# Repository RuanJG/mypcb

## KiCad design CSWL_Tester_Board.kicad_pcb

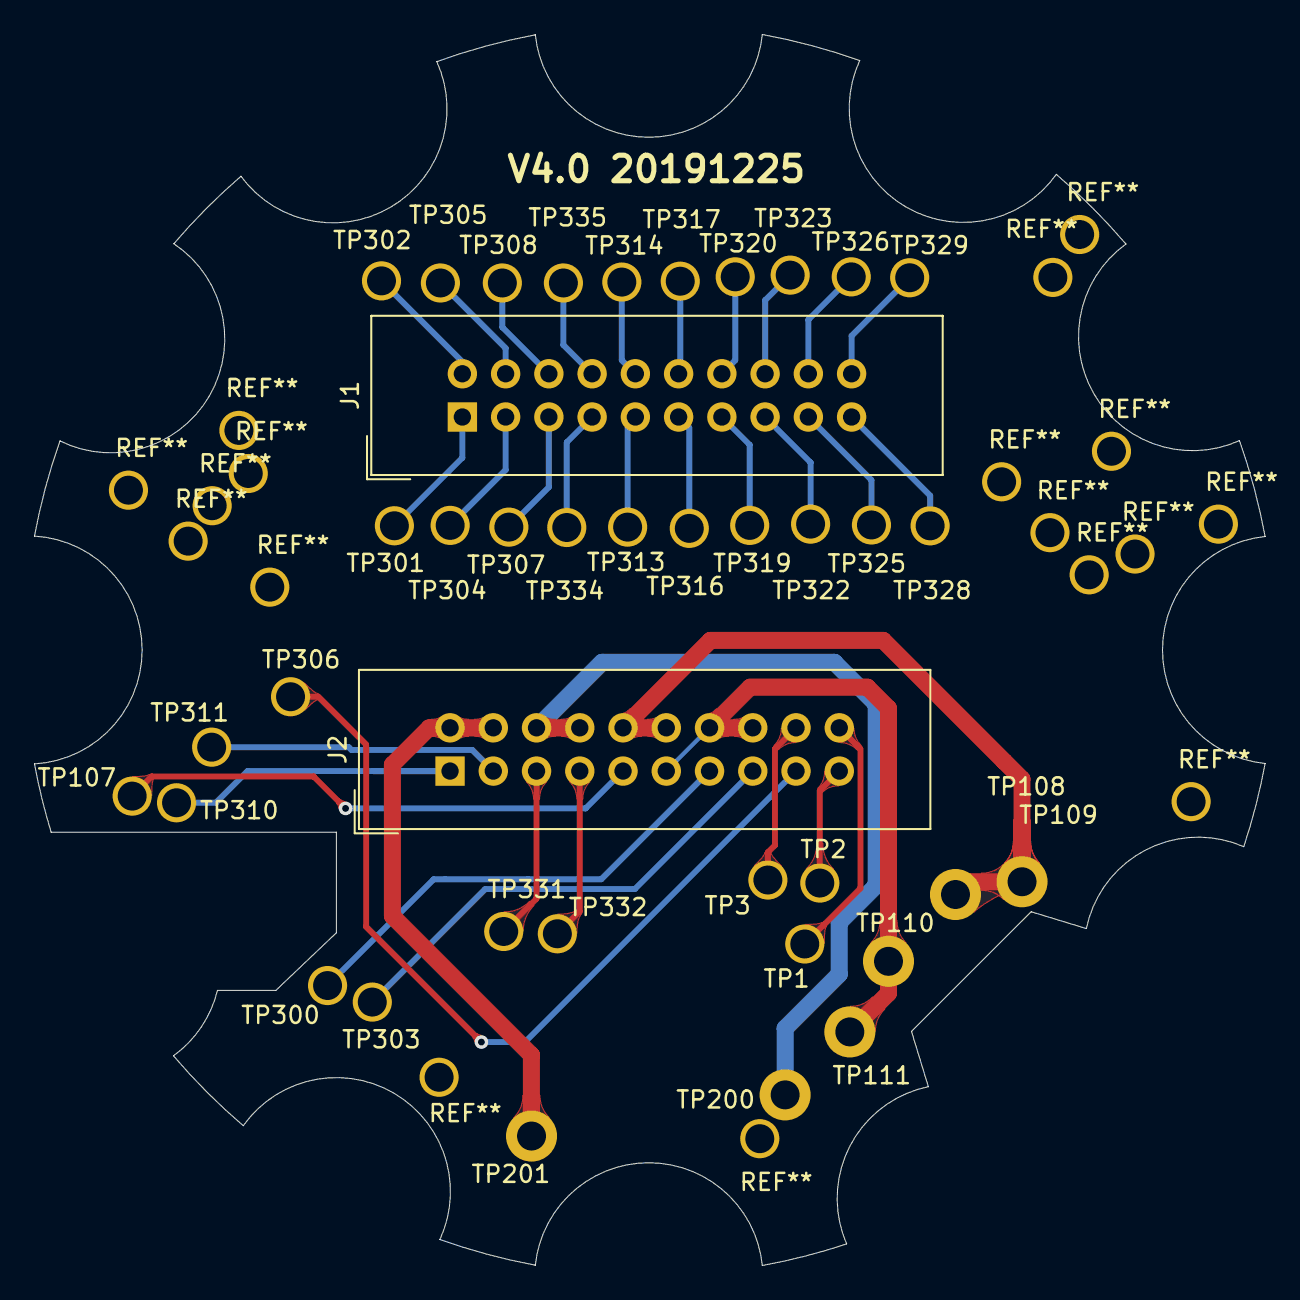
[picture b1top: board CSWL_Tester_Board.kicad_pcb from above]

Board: 2 copper layers, 72.3 x 72.3 mm, 39 parts (0 on the bottom side), 35 nets.

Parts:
J1, J2: Conn_02x10_Odd_Even; IDC-Header_2x10_P2.54mm_Vertical
TP1, TP2, TP3, TP107, TP300, TP301, TP302, TP303, TP304, TP305, TP306, TP307, TP308, TP310, TP311, TP313, TP314, TP316, TP317, TP319, TP320, TP322, TP323, TP325, TP326, TP328, TP329, TP331, TP332, TP334, TP335: TP; PinCard_Hole_D2.3mm_1.3dill
TP108: TP108; PinCard_Hole_D2.3mm_1.3dill
TP109: TP109; PinCard_Hole_D2.3mm_1.3dill
TP110: TP110; PinCard_Hole_D2.3mm_1.3dill
TP111: TP111; PinCard_Hole_D2.3mm_1.3dill
TP200: TP200; PinCard_Hole_D2.3mm_1.3dill
TP201: TP201; PinCard_Hole_D2.3mm_1.3dill

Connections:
/AS4_Y: J2.19, TP1.1
/AS4_Z: J2.20, TP2.1
/CSWL_IN+: J2.10, J2.12, TP108.1, TP109.1
/CSWL_IN-: J2.11, J2.14, J2.16, TP110.1, TP111.1
/CSWL_VDD+: J2.9, TP107.1
/CSWL_Vout+: J2.6, J2.8, TP200.1
/CSWL_Vout-: J2.2, J2.4, TP201.1
/LED1+: J1.1, TP301.1
/LED1-: J1.2, TP302.1
/LED2+: J1.3, TP304.1
/LED2-: J1.4, TP305.1
/LED3+: J1.5, TP307.1
/LED3-: J1.6, TP308.1
/LED4+: J2.1, TP310.1
/LED4-: J2.3, TP311.1
/LED5+: J1.9, TP313.1
/LED5-: J1.10, TP314.1
/LED6+: J1.11, TP316.1
/LED6-: J1.12, TP317.1
/LED7+: J1.13, TP319.1
/LED7-: J1.14, TP320.1
/LED8+: J1.15, TP322.1
/LED8-: J1.16, TP323.1
/LED9+: J1.17, TP325.1
/LED9-: J1.18, TP326.1
/LED10+: J1.19, TP328.1
/LED10-: J1.20, TP329.1
/LED11+: J2.5, TP331.1
/LED11-: J2.7, TP332.1
/LED12+: J1.7, TP334.1
/LED12-: J1.8, TP335.1
/TP300: J2.13, TP300.1
/TP303: J2.15, TP303.1
/TP306: J2.17, TP306.1
/TPXXX: J2.18, TP3.1

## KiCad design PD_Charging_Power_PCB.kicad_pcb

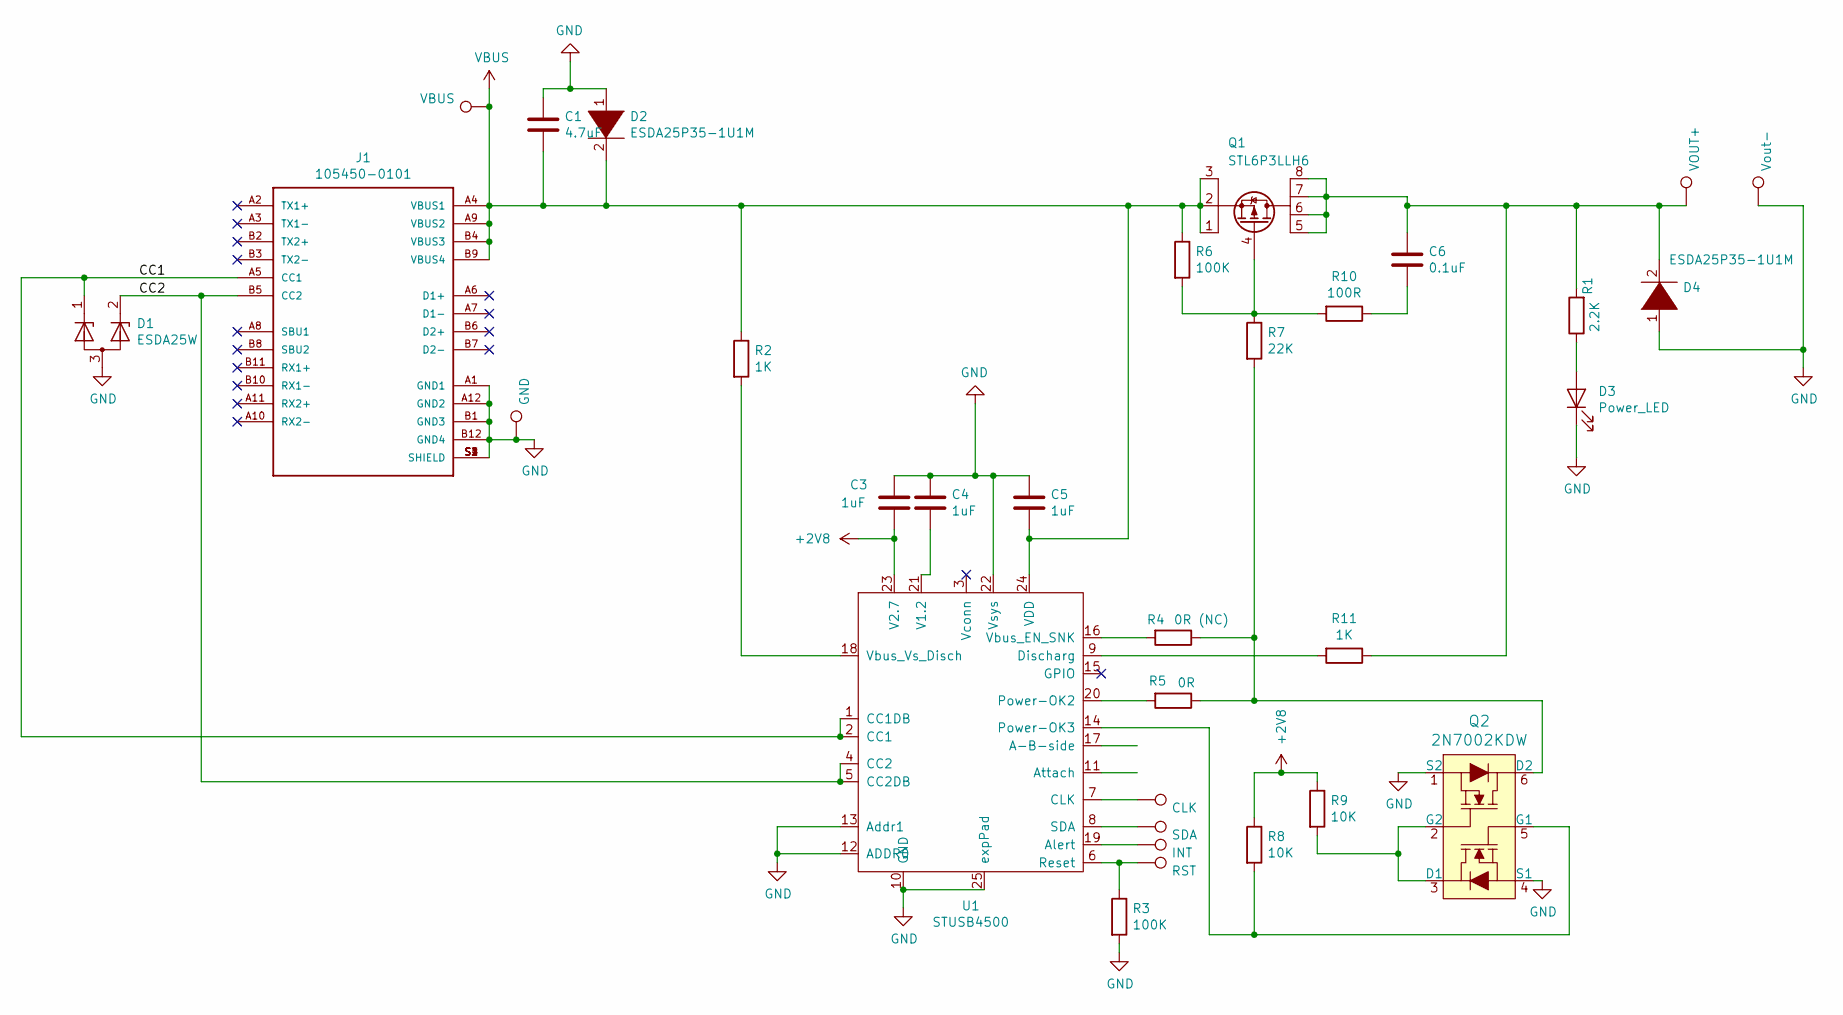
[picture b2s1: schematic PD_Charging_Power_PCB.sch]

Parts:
C1: 4.7uF; C_0603_1608Metric
C3, C4, C5: 1uF; C_0402_1005Metric
C6: 0.1uF; C_0402_1005Metric
CLK1: CLK; TestPoint_Pad_D1.0mm
D1: ESDA25W; SOT-323_SC-70
D2, D4: ESDA25P35-1U1M; QFN 1610
D3: Power_LED; Led-LTST-S270KGKT
GND1: GND; TestPoint_Pad_D1.0mm
INT1: INT; TestPoint_Pad_D1.0mm
J1: 105450-0101; MOLEX_105450-0101
Q1: STL6P3LLH6; PowerFLAT-3x3mm-8pin
Q2: 2N7002KDW; SOT-363_SC-70-6
R1: 2.2K; R_0402_1005Metric
R2, R11: 1K; R_0603_1608Metric
R3, R6: 100K; R_0402_1005Metric
R4: 0R (NC); R_0402_1005Metric
R5: 0R; R_0402_1005Metric
R7: 22K; R_0402_1005Metric
R8, R9: 10K; R_0402_1005Metric
R10: 100R; R_0402_1005Metric
RST1: RST; TestPoint_Pad_D1.0mm
SDA1: SDA; TestPoint_Pad_D1.0mm
U1: STUSB4500; QFN-24-1EP_4x4mm_P0.5mm_EP2.7x2.7mm
VBUS1: VBUS; TestPoint_Pad_D1.0mm
VOUT1: VOUT+; TestPoint_Pad_4mmx3mm
Vout2: Vout-; TestPoint_Pad_4mmx3mm

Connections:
+2V8: C3.2, R8.1, R9.1, U1.23 (V2.7)
/CC1: D1.1 (K), J1.A5 (CC1), U1.1 (CC1DB), U1.2 (CC1)
/CC2: D1.2 (K), J1.B5 (CC2), U1.4 (CC2), U1.5 (CC2DB)
GND: C1.1, C3.1, C4.1, C5.1, D1.3 (A), D2.1 (K), D3.1 (K), D4.1 (K), GND1.1, J1.A1 (GND1), J1.A12 (GND2), J1.B1 (GND3), J1.B12 (GND4), J1.S1 (SHIELD), J1.S2 (SHIELD), J1.S3 (SHIELD), J1.S4 (SHIELD), Q2.1 (S2), Q2.4 (S1), R3.2, U1.10 (GND), U1.12 (ADDR0), U1.13 (Addr1), U1.22 (Vsys), U1.25 (expPad), Vout2.1
unnamed: C4.2, U1.21 (V1.2)
unnamed: C6.1, D4.2 (A), Q1.5 (D), Q1.6 (D), Q1.7 (D), Q1.8 (D), R1.2, R11.1, VOUT1.1
unnamed: C6.2, R10.1
unnamed: CLK1.1, U1.7 (CLK)
unnamed: D3.2 (A), R1.1
unnamed: INT1.1, U1.19 (Alert)
unnamed: Q1.4 (G), R6.2, R7.1, R10.2
unnamed: Q2.2 (G2), Q2.3 (D1), R9.2
unnamed: Q2.5 (G1), R8.2, U1.14 (Power-OK3)
unnamed: Q2.6 (D2), R4.1, R5.1, R7.2
unnamed: R2.2, U1.18 (Vbus_Vs_Disch)
unnamed: R3.1, RST1.1, U1.6 (Reset)
unnamed: R4.2, U1.16 (Vbus_EN_SNK)
unnamed: R5.2, U1.20 (Power-OK2)
unnamed: R11.2, U1.9 (Discharg)
unnamed: SDA1.1, U1.8 (SDA)
VBUS: C1.2, C5.2, D2.2 (A), J1.A4 (VBUS1), J1.A9 (VBUS2), J1.B4 (VBUS3), J1.B9 (VBUS4), Q1.1 (S), Q1.2 (S), Q1.3 (S), R2.1, R6.1, U1.24 (VDD), VBUS1.1

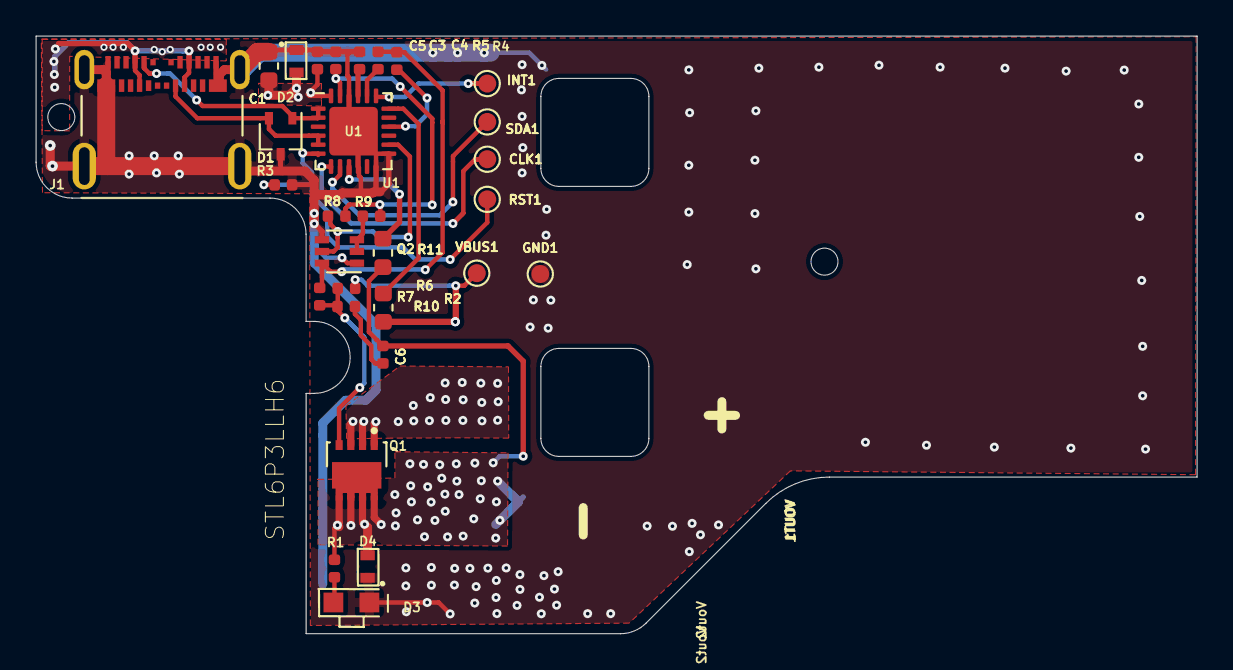
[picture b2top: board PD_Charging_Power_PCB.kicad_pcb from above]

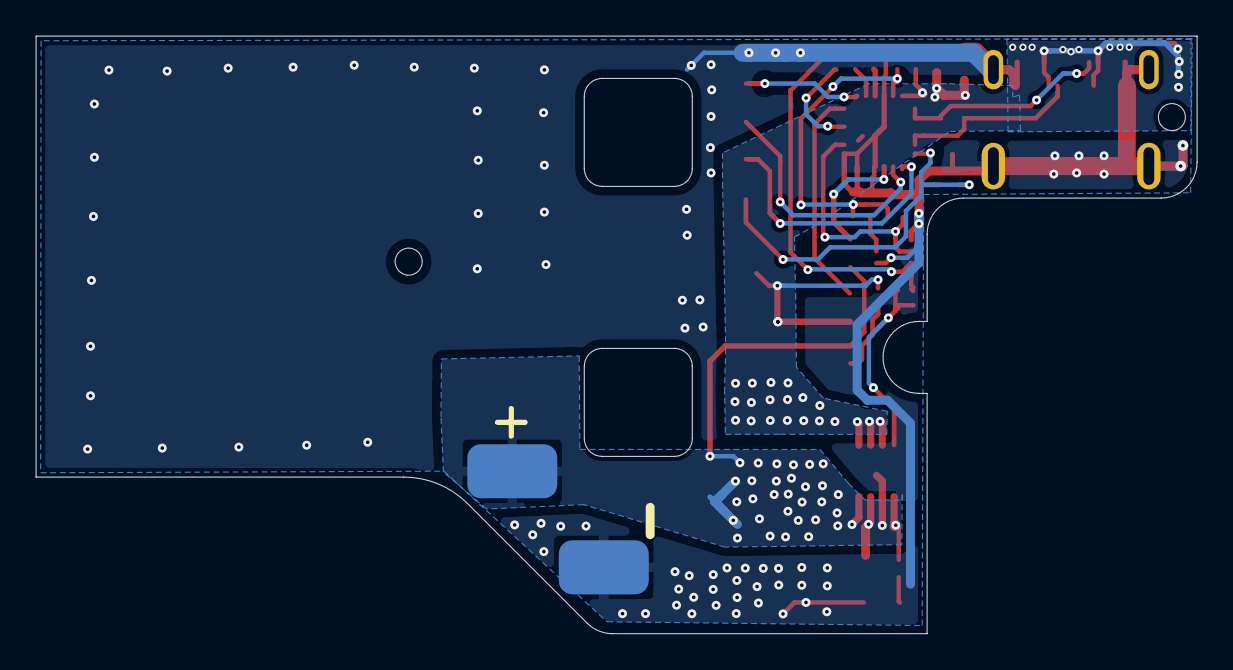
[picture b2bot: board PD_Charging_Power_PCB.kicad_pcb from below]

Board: 2 copper layers, 64.5 x 33.2 mm, 32 parts (2 on the bottom side), 21 nets.

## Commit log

2017-09-30 Ruan: base design
2017-09-30 Ruan: modify for rompa
2017-10-09 Ruan: rename and add ddr3
2017-10-11 Ruan: add ap6212, camera, button, lcd, C_TP ic
2017-10-14 Ruan: base finsih in 10/14
2017-10-14 Ruan: off sheet connector modify
2017-10-16 Ruan: modify 1
2017-10-16 Ruan: add BOM
2017-10-25 Ruan: backup in 20171025
2017-11-16 Ruan: V0
2017-11-21 Ruan: add MP2451DT Snippets
2019-07-10 Ruan: base
2019-07-11 Ruan: add gpio list
2019-07-11 Ruan: modify LED part
2019-07-11 RUan: 12 mcu version
2019-07-13 Ruan: fix
2019-07-16 Ruan: sperate to pin board and led board
2019-07-17 Ruan: fix bug' '
2019-07-17 Ruan: fix 2
2019-07-17 Ruan: fix 3
2019-07-17 Ruan: fix path
2019-07-19 Ruan: make pcb V0
2019-07-19 Ruan： start PCB
2019-07-21 Ruan: board PCB start
2019-07-22 Ruan: pcb developing
2019-07-24 Ruan: base ok V0
2019-07-25 Ruan: improve the crystal path
2019-07-25 Ruan: add more function on ADC connector
2019-07-25 Ruan: change the crystal component
2019-07-26 Ruan: start PCB design
2019-07-28 Ruan: pcb designing
2019-07-28 Ruan： PCB designing
2019-07-29 Ruan: PCB design -> base layout finish
2019-07-30 Ruan: base ok
2019-07-30 Ruan: modify the coper zone
2019-08-02 Ruan: add some components
2019-08-05 Ruan: add treatdrop
2019-08-05 Ruan: add treadrop
2019-08-05 Ruan: modify board shape
2019-08-05 Ruan: modify shape
2019-08-24 Ruan: modify crystal capaccitor
2019-08-24 Ruan: use L9110 control relay
2019-08-24 Ruan: add add sod-123 of diode and L9110
2019-08-28 ruan : version 0
2019-08-28 Ruan: modify for V0.1
2019-09-13 Ruan: base ok V0.1
2019-09-16 Ruan: add treat drop
2019-09-16 Ruan；V0.1B
2019-09-16 Ruan: update to V0.2
2019-09-17 Ruan: fix board Edge bug
2019-09-17 Ruan: remove step file track
2019-10-17 Ruan: back up for V0.2
2019-10-24 Ruan: V0.3
2019-11-11 Ruan: extend the hold size to 1.7
2019-12-24 Ruan: change to V0.5
2019-12-25 Ruan: V4.0 for MP1
